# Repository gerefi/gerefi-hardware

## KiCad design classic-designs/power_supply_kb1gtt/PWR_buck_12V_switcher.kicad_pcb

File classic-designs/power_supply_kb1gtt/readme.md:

Older version of the power supply with SMD inductors

For current version with three inductors see [frankenso-PWR-Supply](../frankenso-PWR-Supply)

https://gerefi.com/forum/viewtopic.php?f=4&t=394

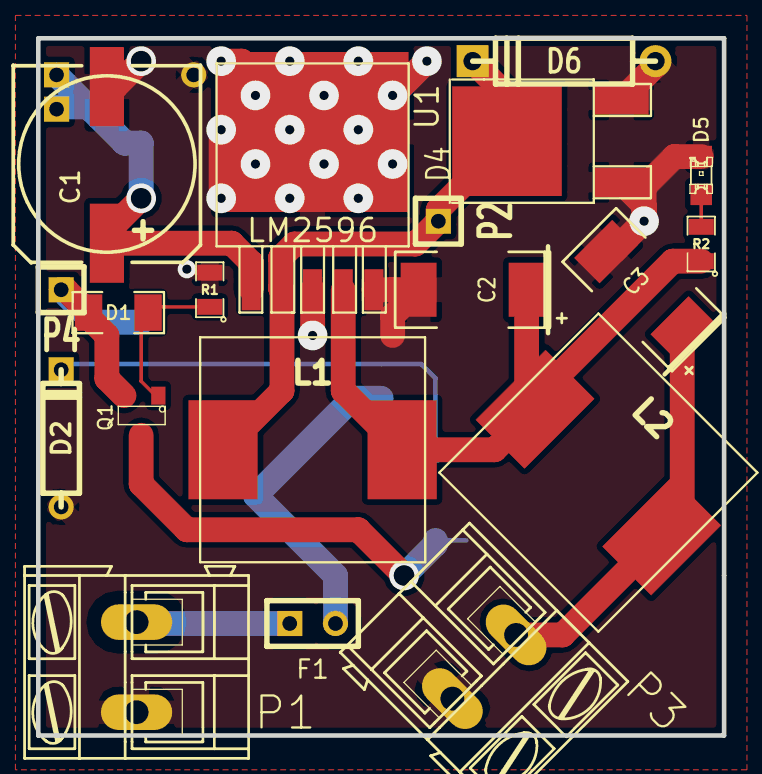
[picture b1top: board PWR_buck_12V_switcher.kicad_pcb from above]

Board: 2 copper layers, 38.1 x 38.7 mm, 24 parts (0 on the bottom side), 12 nets.

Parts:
C1: 330uF 35V; SMDSVP10
C2, C3: 220uF 16V; SM2512
D1: 7.5V; SM1206
D2: 14V; D3
D3: 24V; D3
D4: SCHDPAK; DPAK2
D5: LED-grn; LED-0805
D6: DIODESCH; D4
F1: 5A; SIL-2
L1, L2, L3: 38uH; SM100uH
P1, P3: CONN_2; AK300-2
P2, P4, P5: CONN_1; SIL-1
Q1: 20V; SOT23
Q2: 200V; m-pad-2.1-TO-263AB
R1: 39k; SM0805
R2: 1k; SM0805
R3: 100k; SM0805
U1: LM2596; DPAK5

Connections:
/5V-REG: C3.1, L2.2, P3.1
/FB: C2.1, L1.2, L2.1, R2.1, U1.4
/OUT: D4.2, D6.2, L1.1, P2.1, U1.2
/VBAT: C1.1, D3.2, L3.2, P5.1, U1.1
/Vf: F1.2, Q2.2, R3.1
/Vin: F1.1, P1.2
/Vs1: D2.2, Q2.1, R3.2
/Vs2: Q1.3, Q2.3
GND: C1.2, C2.2, C3.2, D2.1, D3.1, D4.1, D4.3, D5.2, D6.1, P1.1, P3.2, R1.2, U1.3, U1.5
unnamed: D1.1, Q1.1, R1.1
unnamed: D1.2, L3.1, P4.1, Q1.2
unnamed: D5.1, R2.2

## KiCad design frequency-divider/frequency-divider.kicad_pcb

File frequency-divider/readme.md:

We sometimes want to lower input frequency unless one does hard code periperal based magic.

https://github.com/gerefi/gerefi/issues/2935

https://github.com/gerefi/gerefi/issues/3412

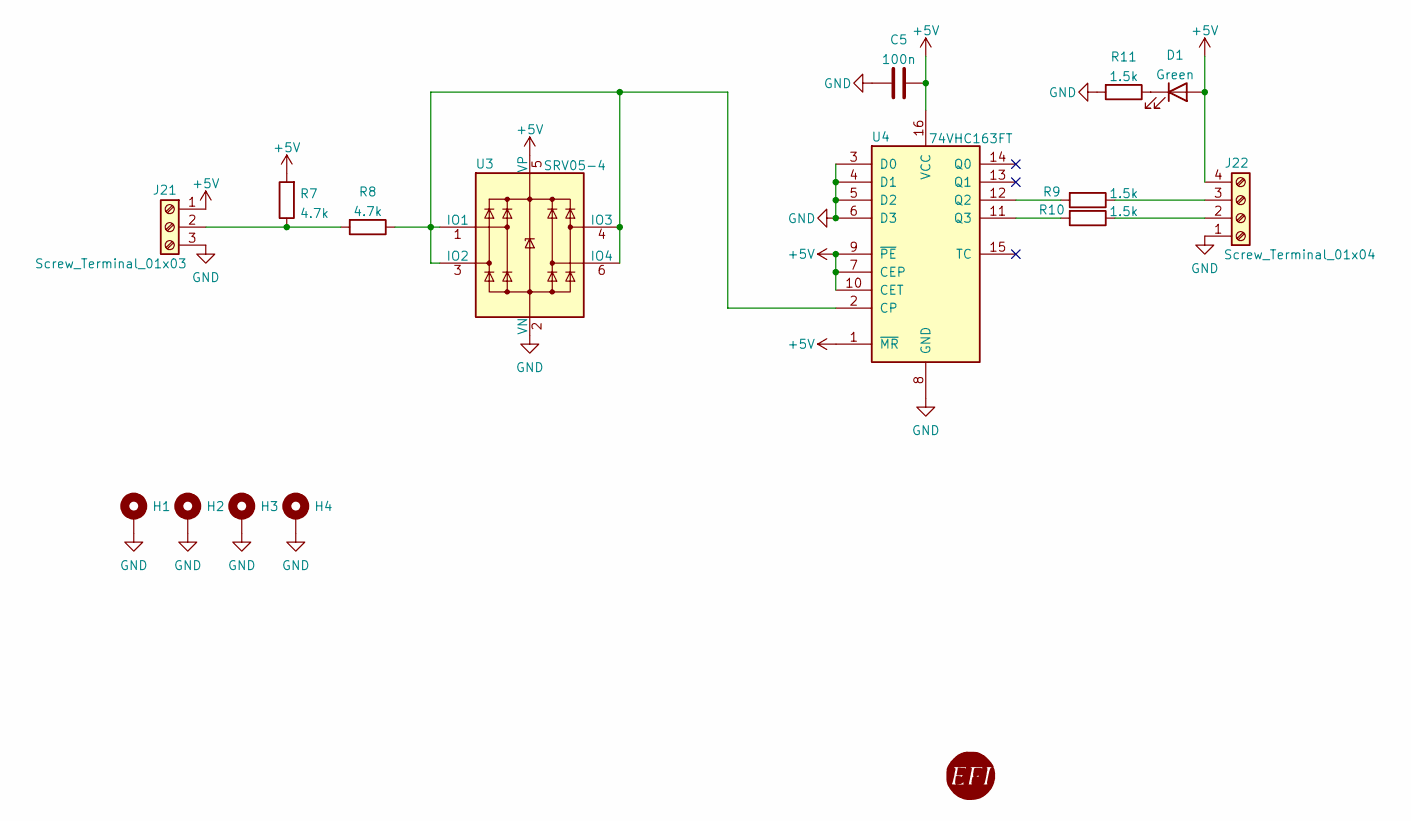
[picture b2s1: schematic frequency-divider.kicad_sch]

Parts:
C5: 100n; C_0603_1608Metric_Pad1.08x0.95mm_HandSolder; LCSC C14663
D1: Green; LED_0805_2012Metric_Pad1.15x1.40mm_HandSolder; LCSC C2297
G8: gerefi_LOGO; gerefi_logo
H1, H2, H3, H4: MountingHole_Pad; MountingHole_3.2mm_M3_Pad_Via
J21: Screw_Terminal_01x03; TerminalBlock_MetzConnect_Type055_RT01503HDWU_1x03_P5.00mm_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; LCSC C128026
J22: Screw_Terminal_01x04; TerminalBlock_MetzConnect_Type055_RT01504HDWU_1x04_P5.00mm_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; LCSC C173286
R7, R8: 4.7k; R_0603_1608Metric_Pad0.98x0.95mm_HandSolder; LCSC C23162
R9, R10, R11: 1.5k; R_0603_1608Metric_Pad0.98x0.95mm_HandSolder; LCSC C22843
U3: SRV05-4; SOT-23-6; LCSC C85364
U4: 74VHC163FT; TSSOP-16_4.4x5mm_P0.65mm; LCSC C150161

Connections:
+5V: C5.2, D1.2 (A), J21.1, J22.4, R7.2, U3.5 (VP), U4.1 (~MR), U4.7 (CEP), U4.9 (~PE), U4.10 (CET), U4.16 (VCC)
GND: C5.1, H1.1, H2.1, H3.1, H4.1, J21.3, J22.1, R11.2, U3.2 (VN), U4.3 (D0), U4.4 (D1), U4.5 (D2), U4.6 (D3), U4.8 (GND)
unnamed: D1.1 (K), R11.1
unnamed: J21.2, R7.1, R8.2
unnamed: J22.2, R10.1
unnamed: J22.3, R9.1
unnamed: R8.1, U3.1 (IO1), U3.3 (IO2), U3.4 (IO3), U3.6 (IO4), U4.2 (CP)
unnamed: R9.2, U4.12 (Q2)
unnamed: R10.2, U4.11 (Q3)

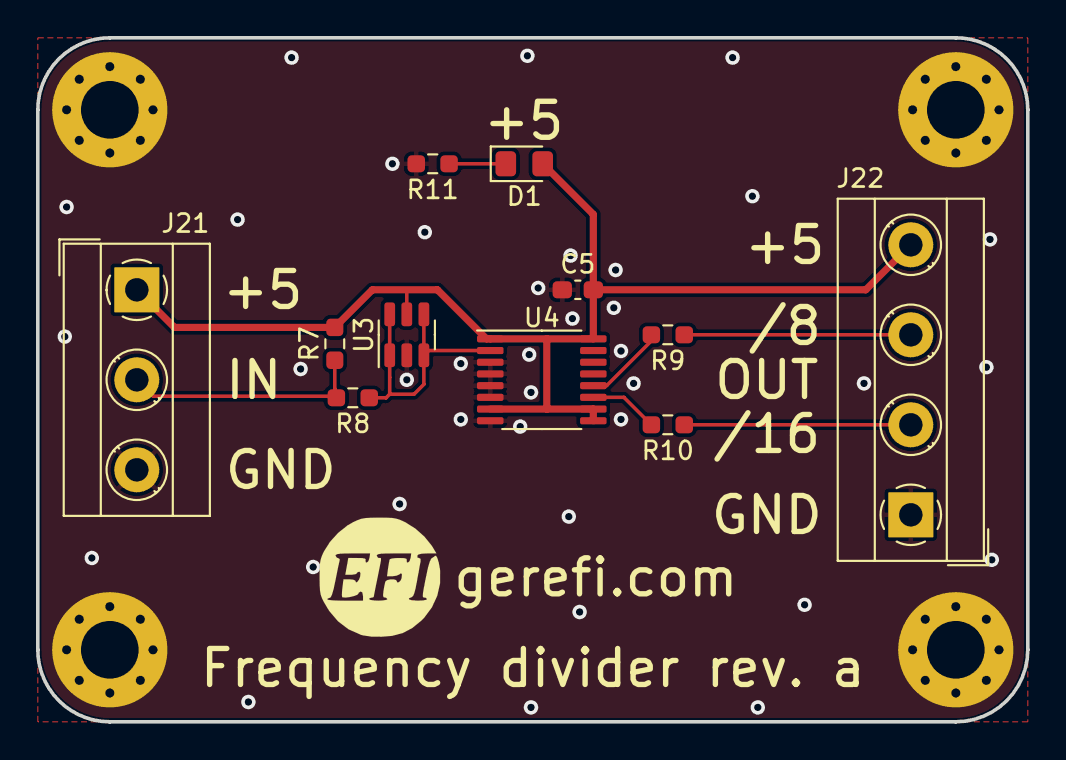
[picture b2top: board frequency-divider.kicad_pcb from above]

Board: 2 copper layers, 55.0 x 38.0 mm, 16 parts (0 on the bottom side), 9 nets.

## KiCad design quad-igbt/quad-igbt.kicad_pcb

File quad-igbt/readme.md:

x4 coil driver

For instance ISL9V3040S3S

See also https://github.com/gerefi/gerefi/tree/master/hardware/DDPAK_breakout

https://www.youtube.com/watch?v=TUJzp6ig_bQ

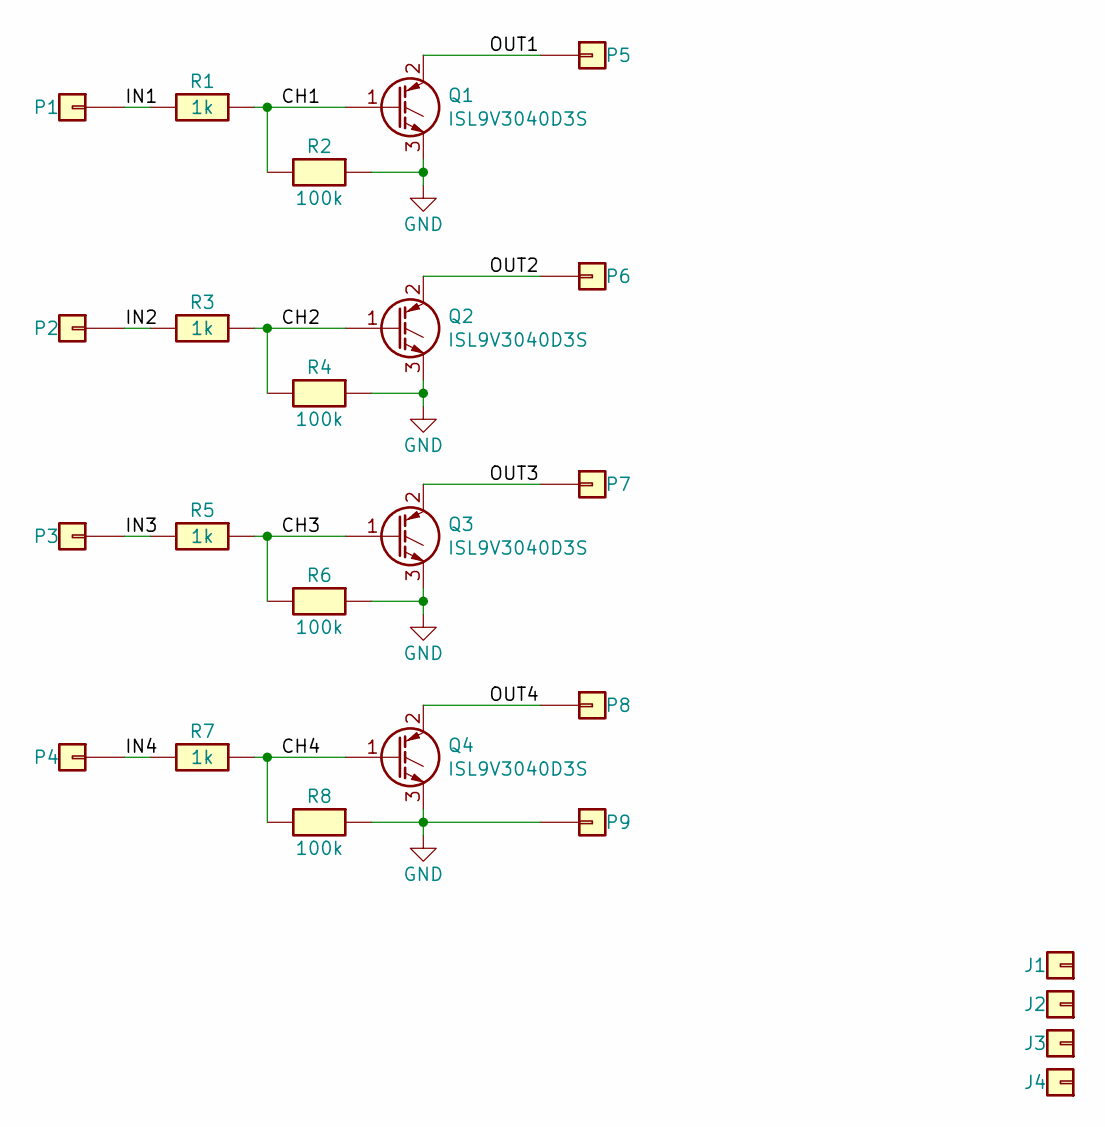
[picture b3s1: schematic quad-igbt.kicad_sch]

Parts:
J1, J2, J3, J4: Conn_01x01; MountingHole_5mm
P1, P2, P3, P4, P5, P6, P7, P8, P9: Pad; PAD-TH
Q1, Q2, Q3, Q4: ISL9V3040D3S; TO-263-2; LCSC C462128
R1, R3, R5, R7: 1k; R0805; LCSC C17513
R2, R4, R6, R8: 100k; R0805; LCSC C149504

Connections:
/CH1: Q1.1 (G), R1.1, R2.2
/CH2: Q2.1 (G), R3.1, R4.2
/CH3: Q3.1 (G), R5.1, R6.2
/CH4: Q4.1 (G), R7.1, R8.2
/IN1: P1.1, R1.2
/IN2: P2.1, R3.2
/IN3: P3.1, R5.2
/IN4: P4.1, R7.2
/OUT1: P5.1, Q1.2 (C)
/OUT2: P6.1, Q2.2 (C)
/OUT3: P7.1, Q3.2 (C)
/OUT4: P8.1, Q4.2 (C)
GND: P9.1, Q1.3 (E), Q2.3 (E), Q3.3 (E), Q4.3 (E), R2.1, R4.1, R6.1, R8.1

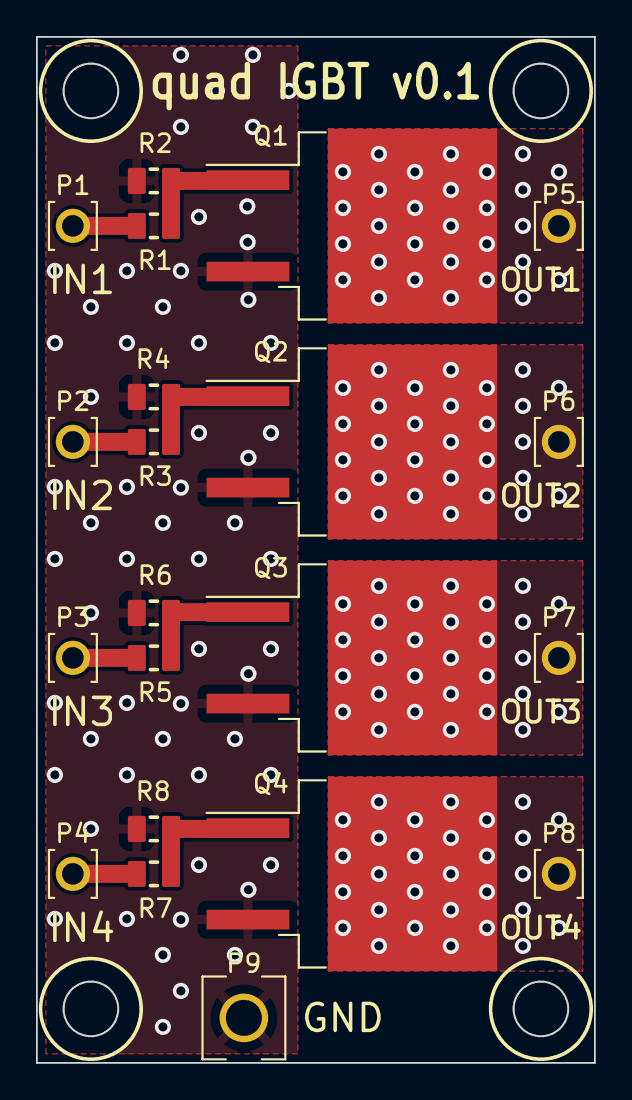
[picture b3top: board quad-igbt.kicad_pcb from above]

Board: 2 copper layers, 31.0 x 57.0 mm, 25 parts (0 on the bottom side), 13 nets.
